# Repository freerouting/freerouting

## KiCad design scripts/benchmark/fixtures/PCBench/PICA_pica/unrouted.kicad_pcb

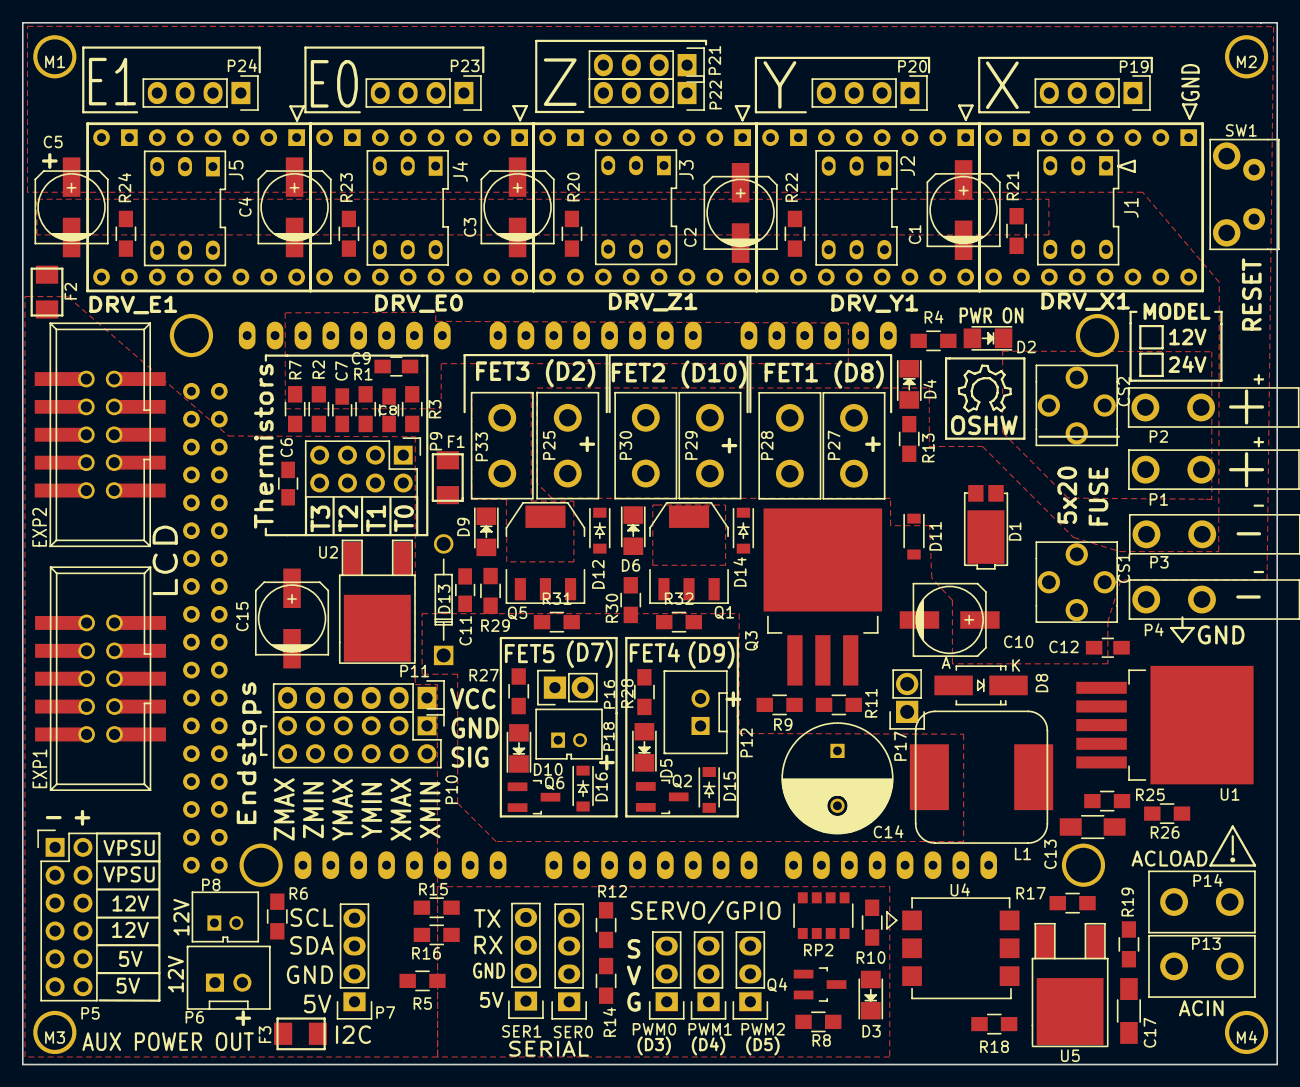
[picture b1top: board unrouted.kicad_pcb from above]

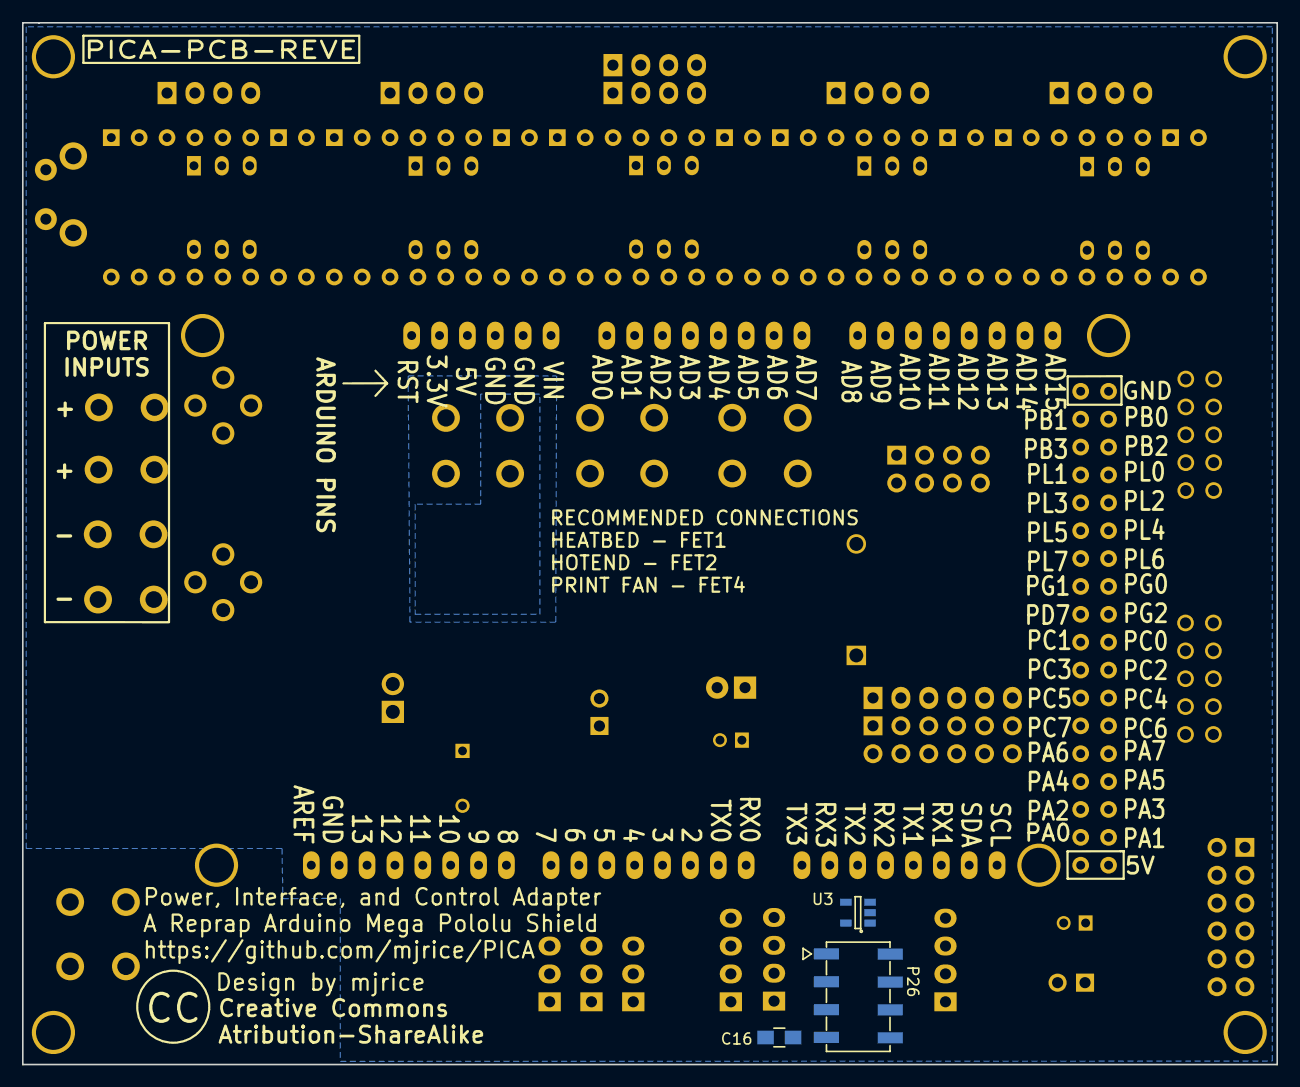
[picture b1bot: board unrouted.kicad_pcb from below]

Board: 2 copper layers, 114.3 x 94.9 mm, 135 parts (3 on the bottom side), 134 nets, no tracks yet.

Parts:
C1, C2, C3, C4, C5, C10, C15: 100UF; c_elec_6.3x5.8
C6, C7, C8, C9, C11, C12, C16: .1UF; C_0805_HandSoldering
C13, C17: 10nF; C_1206_HandSoldering
C14: 470u; C_Radial_D10_L13_P5
CS1, CS2: FUSE_CLIP_5x20; FUSE_CLIP_D_5x20
D1: SBRT20M60SP5-7; POWERDI5
D2: GREEN; LED_1206
D3, D4, D5, D6, D9, D10: Led_Small; LED_1206
D8: MBRA340T3G; SMA_Handsoldering
D11, D12, D14, D15, D16: MBR0560; SOD-123
D13: 1N5333; Diode_Horizontal
DRV_E0, DRV_E1: POLOLU_A4988; SWDIP8_.6W
DRV_X1: POLOLU_A4988; SWDIP8_.6W
DRV_Y1: POLOLU_A4988; SWDIP8_.6W
DRV_Z1: POLOLU_A4988; SWDIP8_.6W
EXP1, EXP2: CONN_02X05; IDC_Header_Straight_10pins_DUAL
F1, F2, F3: 0ZCJ0020FF2E; Fuse_SMD1206_Wave
J1, J2, J3, J4, J5: CONN_02X03; DIP-6_0_ELL
L1: 82uH; RH127
M1, M2, M3, M4: CONN_01X01; MHOLE125
P1, P2, P3, P4: 36-4966-ND; SPADE_CONN_RT
P5, P10: CONN_02X06; Pin_Header_Straight_2x06
P6, P12: JST-XH; JST_XH_2POS
P7, P19, P20, P21, P22, P23, P24: CONN_01X04; Pin_Header_Straight_1x04
P8, P18: JST-PH; JST_PH_2POS
P9: CONN_02X04; Pin_Header_Straight_2x04
P11: CONN_01X06; Pin_Header_Straight_1x06
P13, P14, P25, P27, P28, P29, P30, P33: CONN_01X02; SPACE_CONN_VERT
P16: DUPONT; Pin_Header_Straight_1x02
P17: CONN_01X02; Pin_Header_Straight_1x02
P26: CONN_02X04; PINHEADER_2X4_SMD
PWM0, PWM1, PWM2: CONN_01X03; Pin_Header_Straight_1x03
Q1, Q5: IRFL024ZPbF; SOT-223
Q2, Q4, Q6: IRLML6346; SOT-23_Handsoldering
Q3: IRFZ48VS; TO-263-3Lead
R1, R2, R3, R4, R5, R6, R7, R13, R14, R16, R20, R21, R22, R23, R24, R27, R28, R29, R30: 4.7K; R_0805_HandSoldering
R8, R11: 100K; R_0805_HandSoldering
R9, R19, R31, R32: 50; R_0805_HandSoldering
R10: 200; R_0805_HandSoldering
R12, R15, R26: 2K; R_0805_HandSoldering
R17, R18: 360; R_0805_HandSoldering
R25: 17.2K; R_0805_HandSoldering
RP2: YC164-JR-07150KL; RESARY_4_CTS_744
SER0, SER1: CONN_01X04; Pin_Header_Straight_1x04
SHIELD1: ARDUINO_MEGA_SHIELD; MEGA_NOLINES
SW1: BSF-3100; BSF_RT
U1: LM2596-ADJ; TO-263-5Lead
U2: MC7805BDTRKG; TO-252-2Lead
U3: TLV70033DDC; SOT-23-5
U4: MOC3061M; 6SMD
U5: TRIAC; TO-252-2Lead

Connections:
+5VL: R1.1, R2.1, R3.1, R7.1, SHIELD1.5V
+12V: C13.1, C14.1, D13.1, D15.1, D16.1, F3.2, L1.2, P12.2, P16.2, P17.1, P18.2, R10.1, R25.1, R27.2, R28.2
+VPSU: C1.1, C2.1, C3.1, C4.1, C5.1, C10.1, C12.1, CS1.1, CS1.2, D1.3, D11.1, D12.1, D14.1, DRV_E0.8, DRV_E1.8, DRV_X1.8, DRV_Y1.8, DRV_Z1.8, P5.2, P5.4, P17.2, P25.1, P25.2, P27.1, P27.2, P29.1, P29.2, R13.1, R29.2, R30.2, U1.1
/AM_VIN: C11.1, D13.2, F1.1, U2.1
/DRV_VCC: DRV_E0.2, DRV_E1.2, DRV_X1.2, DRV_Y1.2, DRV_Z1.2, F2.1, J1.1, J1.3, J1.5, J2.1, J2.3, J2.5, J3.1, J3.3, J3.5, J4.1, J4.3, J4.5, J5.1, J5.3, J5.5, R20.1, R21.1, R22.1, R23.1, R24.1
/FB_ADJ: C13.2, R25.2, R26.1, U1.4
/FE1_D: D5.1, D15.2, P12.1, Q2.3
/FE2_D: D10.1, D16.2, P16.1, P18.1, Q6.3
/HE1_D: D6.1, D14.2, P30.1, P30.2, Q1.2, Q1.4
/HE1_G: Q1.1, R32.1
/HE2_D: D9.1, D12.2, P33.1, P33.2, Q5.2, Q5.4
/HE2_G: Q5.1, R31.1
/MISO: EXP2.1, SHIELD1.50
/MOSI: EXP2.6, SHIELD1.51
/Q3_D: D4.1, D11.2, P28.1, P28.2, Q3.2, Q3.4
/SCK: EXP2.2, SHIELD1.52
/SDSS: EXP2.4, SHIELD1.53
/SD_CARD_DET: EXP2.7, SHIELD1.49
/TX1_S: P26.8, R15.1, R16.1, SER1.4
/VAA_IN: CS2.1, CS2.2, P1.1, P1.2, P2.1, P2.2
BED_EN: R9.2, R11.1, SHIELD1.8
BTN_EN1: EXP2.3, SHIELD1.47
BTN_EN2: EXP2.5, SHIELD1.48
BTN_ENC: EXP1.2, SHIELD1.31
E0_DIR: DRV_E0.16, SHIELD1.24
E0_EN: DRV_E0.9, R23.2, SHIELD1.26
E0_STEP: DRV_E0.15, SHIELD1.AD13
E1_DIR: DRV_E1.16, SHIELD1.28
E1_EN: DRV_E1.9, R24.2, SHIELD1.27
E1_STEP: DRV_E1.15, SHIELD1.AD14
FAN2_EN: Q6.1, RP2.3, SHIELD1.7
FAN_EN: Q2.1, RP2.2, SHIELD1.9
GND: C1.2, C2.2, C3.2, C4.2, C5.2, C6.2, C7.2, C8.2, C9.2, C10.2, C11.2, C12.2, C14.2, C15.2, C16.2, D1.1, D1.2, D2.1, D8.2, DRV_E0.1, DRV_E0.7, DRV_E1.1, DRV_E1.7, DRV_X1.1, DRV_X1.7, DRV_Y1.1, DRV_Y1.7, DRV_Z1.1, DRV_Z1.7, EXP1.9, P3.1, P3.2, P4.1, P4.2, P5.1, P5.3, P5.5, P5.7, P5.9, P5.11, P6.1, P7.2, P8.1, P9.2, P9.4, P9.6, P9.8, P10.1, P10.3, P10.5, P10.7, P10.9, P10.11, P26.2, PWM0.1, PWM1.1, PWM2.1, Q1.3, Q2.2, Q3.3, Q4.2, Q5.3, Q6.2, R8.2, R11.2, R14.2, R16.2, R26.2, RP2.5, RP2.6, RP2.7, RP2.8, SER0.2, SER1.2, SHIELD1.GND1, SHIELD1.GND2, SHIELD1.GND3, SHIELD1.GND4, SHIELD1.GND5, SW1.1, U1.3, U1.5, U2.2, U3.2
HOTEND2_EN: R31.2, RP2.4, SHIELD1.2
HOTEND_EN: R32.2, RP2.1, SHIELD1.10
KILL_PIN: EXP2.8, SHIELD1.41
LCD_BEEPER: EXP1.1, SHIELD1.29
LCD_D4: EXP1.5, SHIELD1.35
LCD_D5: EXP1.6, SHIELD1.32
LCD_D6: EXP1.7, SHIELD1.37
LCD_D7: EXP1.8, SHIELD1.36
LCD_EN: EXP1.3, SHIELD1.30
LCD_RS: EXP1.4, SHIELD1.33
unnamed: C16.1, P26.3, P26.7, U3.5
unnamed: C17.1, P13.1, P13.2, R18.1, U5.2
unnamed: C17.2, R19.1
unnamed: D2.2, R4.2
unnamed: D3.1, U4.1
unnamed: D3.2, R10.2
unnamed: D4.2, R13.2
unnamed: D5.2, R28.1
unnamed: D6.2, R30.1
unnamed: D8.1, L1.1, U1.2
unnamed: D9.2, R29.1
unnamed: D10.2, R27.1
unnamed: DRV_E0.3, P23.1
unnamed: DRV_E0.4, P23.2
unnamed: DRV_E0.5, P23.3
unnamed: DRV_E0.6, P23.4
unnamed: DRV_E0.10, J4.6
unnamed: DRV_E0.11, J4.4
unnamed: DRV_E0.12, J4.2
unnamed: DRV_E0.13, DRV_E0.14
unnamed: DRV_E1.3, P24.1
unnamed: DRV_E1.4, P24.2
unnamed: DRV_E1.5, P24.3
unnamed: DRV_E1.6, P24.4
unnamed: DRV_E1.10, J5.6
unnamed: DRV_E1.11, J5.4
unnamed: DRV_E1.12, J5.2
unnamed: DRV_E1.13, DRV_E1.14
unnamed: DRV_X1.3, P19.1
unnamed: DRV_X1.4, P19.2
unnamed: DRV_X1.5, P19.3
unnamed: DRV_X1.6, P19.4
unnamed: DRV_X1.10, J1.6
unnamed: DRV_X1.11, J1.4
unnamed: DRV_X1.12, J1.2
unnamed: DRV_X1.13, DRV_X1.14
unnamed: DRV_Y1.3, P20.1
unnamed: DRV_Y1.4, P20.2
unnamed: DRV_Y1.5, P20.3
unnamed: DRV_Y1.6, P20.4
unnamed: DRV_Y1.10, J2.6
unnamed: DRV_Y1.11, J2.4
unnamed: DRV_Y1.12, J2.2
unnamed: DRV_Y1.13, DRV_Y1.14
unnamed: DRV_Z1.3, P21.1, P22.1
unnamed: DRV_Z1.4, P21.2, P22.2
unnamed: DRV_Z1.5, P21.3, P22.3
unnamed: DRV_Z1.6, P21.4, P22.4
unnamed: DRV_Z1.10, J3.6
unnamed: DRV_Z1.11, J3.4
unnamed: DRV_Z1.12, J3.2
unnamed: DRV_Z1.13, DRV_Z1.14
unnamed: F1.2, R4.1, SHIELD1.V_IN
unnamed: F3.1, P5.6, P5.8, P6.2, P8.2
unnamed: P14.1, P14.2, R17.2, R19.2, U5.1
unnamed: Q3.1, R9.1
unnamed: Q4.3, U4.2
unnamed: R12.1, R14.1, SER0.4
unnamed: R17.1, U4.4, U5.3
unnamed: R18.2, U4.6
unnamed: SHIELD1.RST, SW1.2
PWM0: PWM0.3, SHIELD1.3
PWM1: PWM1.3, SHIELD1.4
PWM2: PWM2.3, SHIELD1.5
RX0: SER0.3, SHIELD1.0
RX1: P26.1, SER1.3, SHIELD1.19
SCL: P7.4, R6.2, SHIELD1.21
SDA: P7.3, R5.2, SHIELD1.20
SSR_EN: Q4.1, R8.1, SHIELD1.6
THERM0: C9.1, P9.1, R3.2, SHIELD1.AD9
THERM1: C8.1, P9.3, R1.2, SHIELD1.AD10
THERM2: C7.1, P9.5, R2.2, SHIELD1.AD11
THERM3: C6.1, P9.7, R7.2, SHIELD1.AD12
TX0: R12.2, SHIELD1.1
TX1: R15.2, SHIELD1.18
VCC: C15.1, EXP1.10, F2.2, P5.10, P5.12, P7.1, P11.1, P11.2, P11.3, P11.4, P11.5, P11.6, PWM0.2, PWM1.2, PWM2.2, R5.1, R6.1, SER0.1, SER1.1, U2.3, U3.1, U3.3
X_DIR: DRV_X1.16, SHIELD1.AD0
X_EN: DRV_X1.9, R21.2, SHIELD1.AD6
X_MAX: P10.4, SHIELD1.15
X_MIN: P10.2, SHIELD1.14
X_STEP: DRV_X1.15, SHIELD1.AD1
Y_DIR: DRV_Y1.16, SHIELD1.AD2
Y_EN: DRV_Y1.9, R22.2, SHIELD1.AD7
Y_MAX: P10.8, SHIELD1.17
Y_MIN: P10.6, SHIELD1.16
Y_STEP: DRV_Y1.15, SHIELD1.AD3
Z_DIR: DRV_Z1.16, SHIELD1.AD4
Z_EN: DRV_Z1.9, R20.2, SHIELD1.AD8
Z_MAX: P10.12, SHIELD1.22
Z_MIN: P10.10, SHIELD1.23
Z_STEP: DRV_Z1.15, SHIELD1.AD5

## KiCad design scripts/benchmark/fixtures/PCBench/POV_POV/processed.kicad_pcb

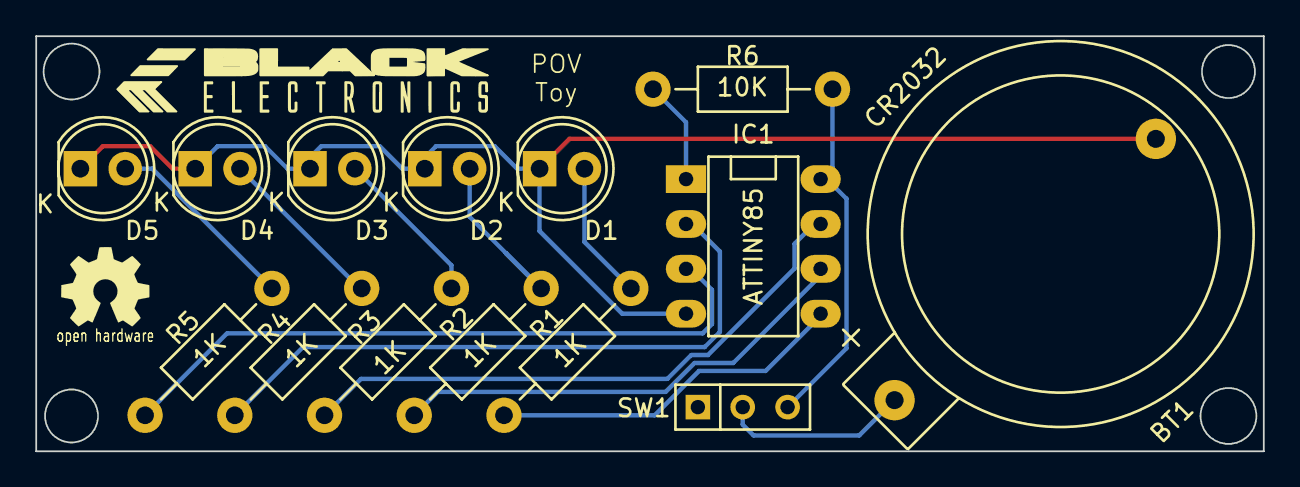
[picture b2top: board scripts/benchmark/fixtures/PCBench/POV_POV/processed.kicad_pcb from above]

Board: 2 copper layers, 69.5 x 23.5 mm, 16 parts (0 on the bottom side), 14 nets.

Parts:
BT1: CR2032; CR2032H
D1, D2, D3, D4, D5: LED; LED-5MM
IC1: ATTINY85; DIP-8__300_ELL
P1: Logo; 3k5
P2: openHW; oshw-logo-kicad-copper-10mm
R1, R2, R3, R4, R5: 1K; Resistor_Horizontal_RM10mm
R6: 10K; Resistor_Horizontal_RM10mm
SW1: SPDT; SW_Micro_SPST

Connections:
/3V3: IC1.8, R6.2, SW1.3
/D0: D1.2, R1.2
/D1: D2.2, R2.2
/D2: D3.2, R3.2
/D3: D4.2, R4.2
/D4: D5.2, R5.2
/MISO: IC1.6, R2.1
/MOSI: IC1.5, R1.1
/SCK: IC1.7, R3.1
/~R: IC1.1, R6.1
GND: BT1.2, D1.1, D2.1, D3.1, D4.1, D5.1, IC1.4
unnamed: BT1.1, SW1.2
unnamed: IC1.2, R4.1
unnamed: IC1.3, R5.1

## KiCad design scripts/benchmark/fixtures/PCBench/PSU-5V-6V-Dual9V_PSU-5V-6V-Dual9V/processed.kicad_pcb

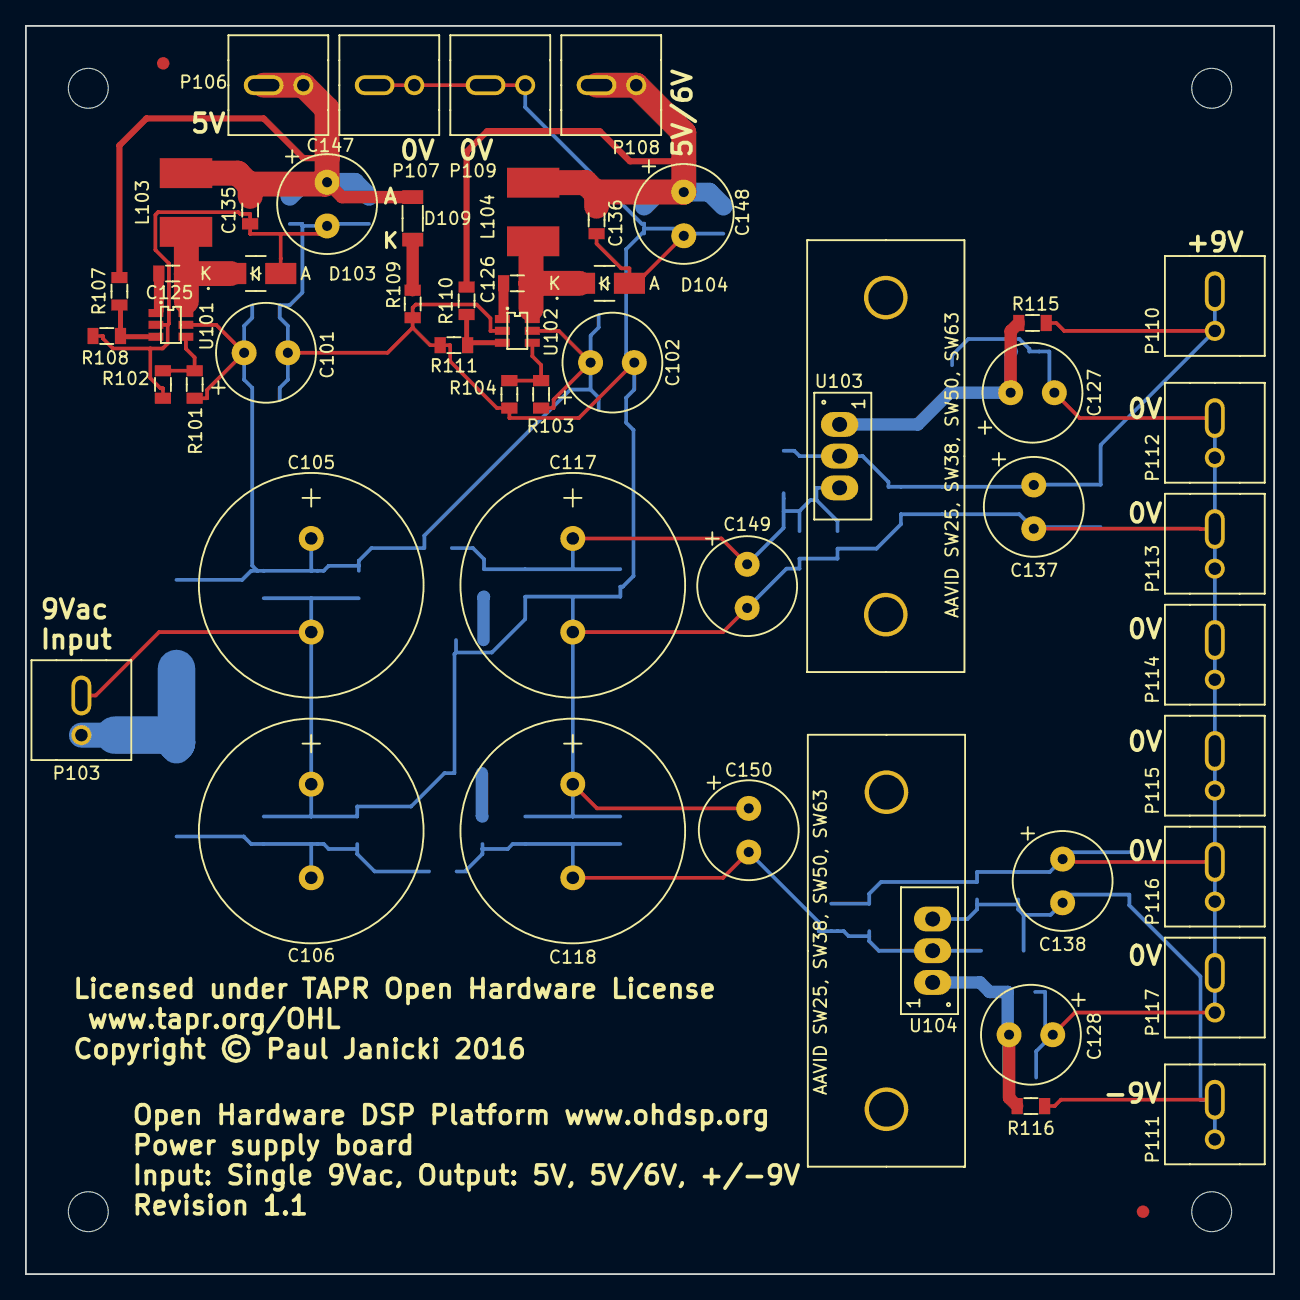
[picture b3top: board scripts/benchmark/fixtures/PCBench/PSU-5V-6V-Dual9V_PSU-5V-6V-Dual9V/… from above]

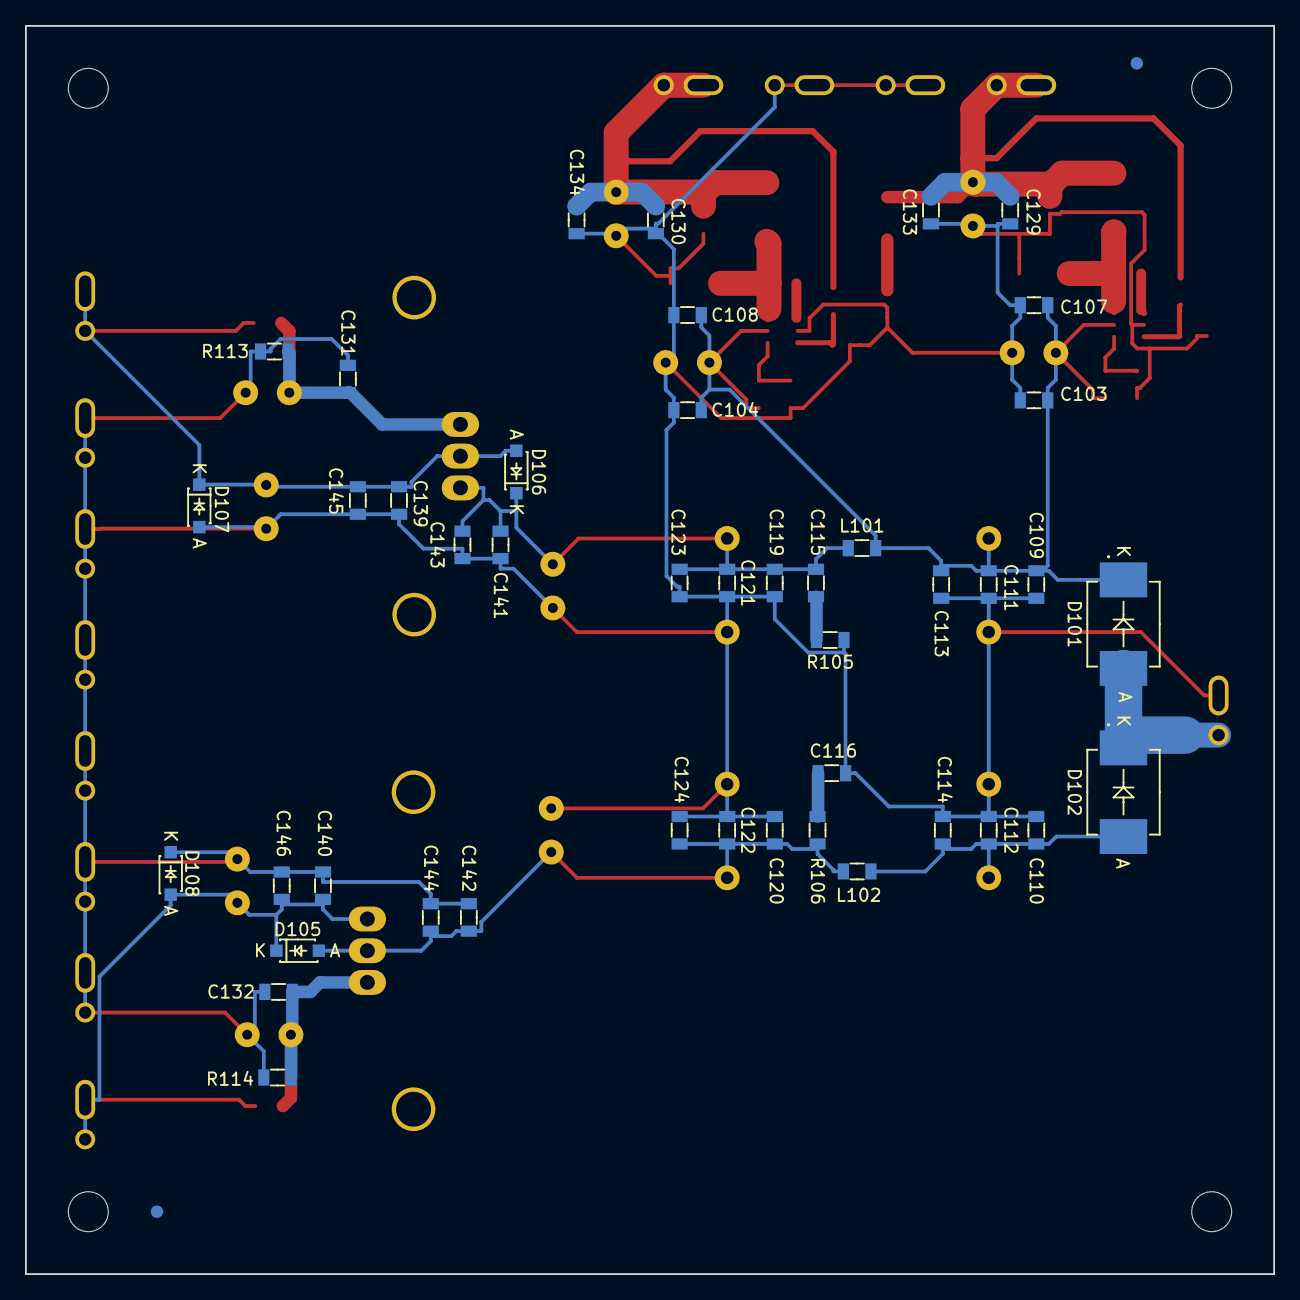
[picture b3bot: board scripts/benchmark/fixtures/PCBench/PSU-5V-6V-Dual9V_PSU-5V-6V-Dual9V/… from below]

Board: 2 copper layers, 100.0 x 100.0 mm, 103 parts (46 on the bottom side), 23 nets.

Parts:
C101, C102, C127, C128, C137, C138, C147, C148, C149, C150: 220u; CAP-TH-D8mmP3.5mm
C103, C104, C109, C110, C119, C120, C129, C130, C133, C134, C141, C142, C145, C146: 22u; SMD-0805
C105, C106, C117, C118: 2200u; CAP-TH-D18mmP7.5mm
C107, C108, C111, C112, C121, C122, C131, C132, C135, C136, C139, C140, C143, C144: 100n; SMD-0805
C113, C114, C123, C124, C125, C126: 10n; SMD-0805
C115, C116: 100p; SMD-0805
D101, D102: ES3D; DIODE-SMC
D103, D104: B240A; DIODE-SMA
D105, D106, D107, D108: SS14L; DIODE-SOD-123
D109: Green LED 1206; SMD-1206
FID1, FID2, FID3, FID4: MNT_HOLE; FID-1MM-3MM
L101, L102: 600R@100MHz; SMD-0805
L103, L104: TYS50406R8M-10; IND-TYS5040-HS
MNT1, MNT2, MNT3, MNT4: MNT_HOLE; MNT_HOLE_3.2mm
P103, P106, P107, P108, P109, P110, P111, P112, P113, P114, P115, P116, P117: CONN_2x1; CONN-2WAY-2.54mm-3.81mm-SPACING
R101, R103: 475k; SMD-0805
R102, R104: 100k; SMD-0805
R105, R106: 47; SMD-0805
R107: 53k6; SMD-0805
R108, R111: 10k; SMD-0805
R109: 470; SMD-0805
R110: 66k5; SMD-0805
R113, R114: 750; SMD-0805
R115, R116: 120; SMD-0805
U101, U102: ADP2301AUJZ; IC-SOT23-6
U103: LM317; IC-TO220-HS-SW25-2G
U104: LM337; IC-TO220-HS-SW25-2G

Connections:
+5V: C129.1, C133.1, C135.1, C147.1, D109.1, L103.2, P106.1, P106.2, R107.1
GNDA: C101.2, C102.2, C103.2, C104.2, C105.2, C106.1, C107.2, C108.2, C109.2, C110.1, C111.2, C112.1, C113.2, C114.1, C116.1, C117.2, C118.1, C119.2, C120.1, C121.2, C122.1, C123.2, C124.1, C127.2, C128.1, C129.2, C130.2, C131.2, C132.1, C133.2, C134.2, C135.2, C136.2, C137.2, C138.1, C139.2, C140.1, C141.2, C142.1, C143.2, C144.1, C145.2, C146.1, C147.2, C148.2, C149.2, C150.1, D103.1, D104.1, D107.1, D108.2, P103.2, P107.1, P107.2, P109.1, P109.2, P112.1, P112.2, P113.1, P113.2, P114.1, P114.2, P115.1, P115.2, P116.1, P116.2, P117.1, P117.2, R102.2, R104.2, R105.2, R108.1, R109.1, R111.1, R113.1, R114.2, U101.2, U102.2
unnamed: C106.2, C110.2, C112.2, C114.2, D102.1, L102.1
unnamed: C115.1, C117.1, C119.1, C121.1, C123.1, C141.1, C143.1, C149.1, D106.2, L101.2, U103.3
unnamed: C115.2, R105.1
unnamed: C116.2, R106.1
unnamed: C118.2, C120.2, C122.2, C124.2, C142.2, C144.2, C150.2, D105.1, L102.2, R106.2, U104.2
unnamed: C125.1, D103.2, L103.1, U101.6
unnamed: C125.2, U101.1
unnamed: C126.1, D104.2, L104.1, U102.6
unnamed: C126.2, U102.1
unnamed: C127.1, C131.1, R113.2, R115.1, U103.1
unnamed: C128.2, C132.2, R114.1, R116.1, U104.1
unnamed: C130.1, C134.1, C136.1, C148.1, L104.2, P108.1, P108.2, R110.1
unnamed: C137.1, C139.1, C145.1, D106.1, D107.2, P110.1, P110.2, R115.2, U103.2
unnamed: C138.2, C140.2, C146.2, D105.2, D108.1, P111.1, P111.2, R116.2, U104.3
unnamed: D101.1, D102.2, P103.1
unnamed: D109.2, R109.2
unnamed: R101.1, R102.1, U101.4
unnamed: R103.1, R104.1, U102.4
unnamed: R107.2, R108.2, U101.3
unnamed: R110.2, R111.2, U102.3
VCC: C101.1, C102.1, C103.1, C104.1, C105.1, C107.1, C108.1, C109.1, C111.1, C113.1, D101.2, L101.1, R101.2, R103.2, U101.5, U102.5

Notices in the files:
scripts/benchmark/fixtures/PCBench/PICA_pica/unrouted.kicad_pcb:
Creative Commons
Atribution-ShareAlike
scripts/benchmark/fixtures/PCBench/PSU-5V-6V-Dual9V_PSU-5V-6V-Dual9V/processed.kicad_pcb:
Licensed under the TAPR Open Hardware License (www.tapr.org/OHL). This documentation
Copyright Paul Janicki 2016
Licensed under TAPR Open Hardware License
Copyright © Paul Janicki 2016
